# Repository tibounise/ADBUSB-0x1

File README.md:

# ADB/USB rev 0x1

Ce repository concerne la première révision du convertisseur ADB/USB (0x1).

Ce convertisseur, basé sur le firmware [tmk_keyboard](tmk/tmk_keyboard), permet de brancher un clavier ADB en USB.

Le repository contient actuellement un guide pour hacker son convertisseur. Il a été écrit avec [LaTeX](http://www.latex-project.org). Une version PDF compilée est disponible pour ceux qui n'auraient pas envie d'installer un compilateur LaTeX sur leur machine.

Il contient aussi le schéma ainsi que le typon du circuit imprimé. Ces fichiers ont étés conçus à l'aide du logiciel [CadSoft EAGLE](http://www.cadsoft.de/eagle-pcb-design-software).

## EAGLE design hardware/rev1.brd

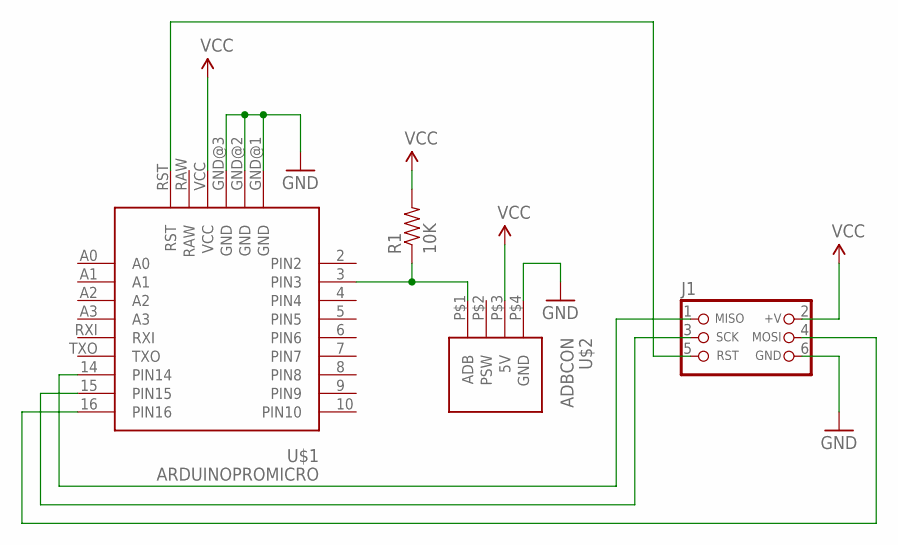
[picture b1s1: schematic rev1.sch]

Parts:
J1: CON_HEADER_PRG_AVR_ICSP-PTH; HEADER_PRG_2X03
R1: 10K; 1206
U$1: ARDUINOPROMICRO; DIP
U$2: ADBCON

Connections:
GND: J1.6 (GND), U$1.GND@1 (GND), U$1.GND@2 (GND), U$1.GND@3 (GND), U$2.P$4 (GND)
unnamed: R1.1, U$1.3 (PIN3), U$2.P$1 (ADB)
unnamed: J1.3 (SCK), U$1.15 (PIN15)
unnamed: J1.5 (RST), U$1.RST
unnamed: J1.1 (MISO), U$1.14 (PIN14)
unnamed: J1.4 (MOSI), U$1.16 (PIN16)
VCC: J1.2 (+V), R1.2, U$1.VCC, U$2.P$3 (5V)

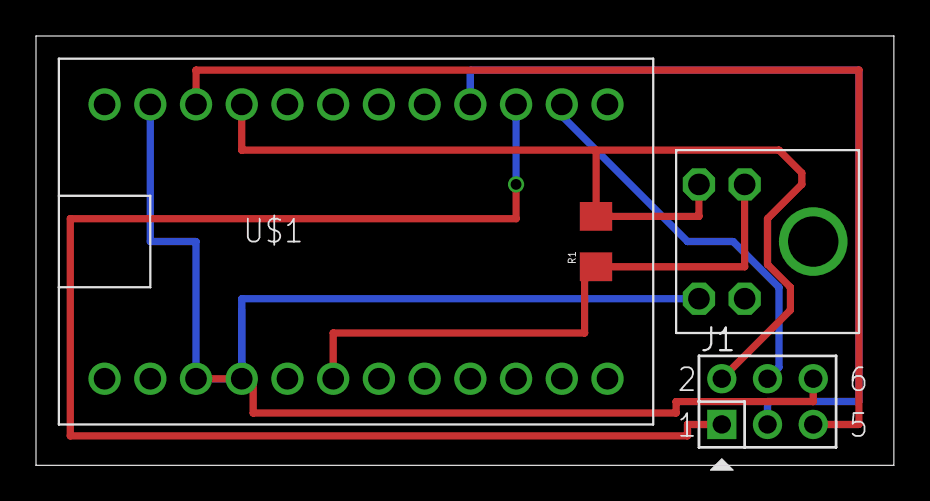
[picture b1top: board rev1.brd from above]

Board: 2 copper layers, 47.7 x 23.9 mm, 4 parts (0 on the bottom side), 7 nets.

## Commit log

2014-10-26 Initial commit of the guides
2014-10-26 Updating hacking guide
2014-10-27 Finished hacking guide
2014-10-27 Adding README
2014-10-27 Adding hardware source
2014-10-27 Adding LICENSE

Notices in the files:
parts and their libraries:
SparkFun-Passives: Licensing: Creative Commons ShareAlike 4.0 International - https://creativecommons.org/licenses/by-sa/4.0
